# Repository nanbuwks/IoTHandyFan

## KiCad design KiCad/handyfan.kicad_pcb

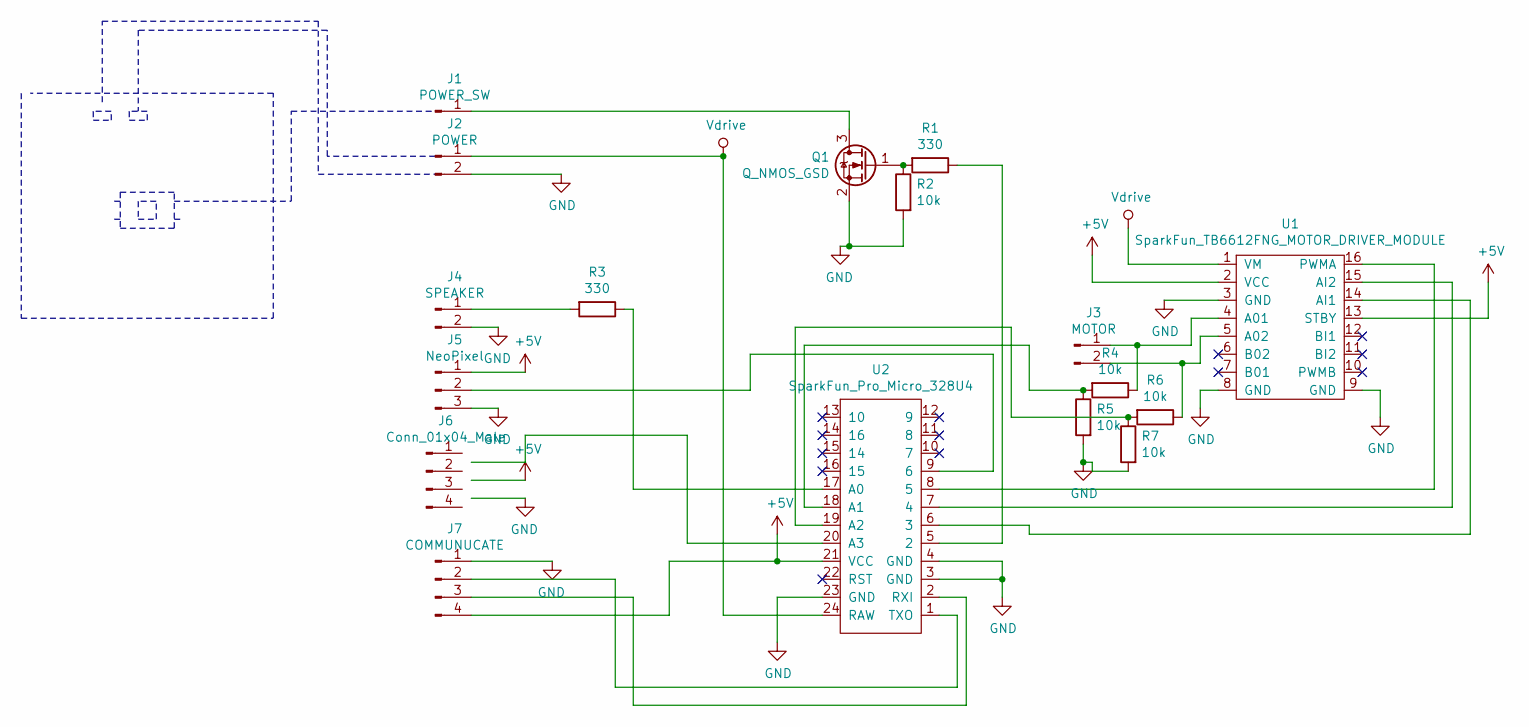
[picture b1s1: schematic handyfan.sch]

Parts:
J1: POWER_SW; PinHeader_1x01_P2.54mm_Vertical
J2: POWER; PinHeader_1x02_P2.54mm_Vertical
J3: MOTOR; PinHeader_1x02_P2.54mm_Vertical
J4: SPEAKER; PinHeader_1x02_P2.54mm_Vertical
J5: NeoPixel; PinHeader_1x03_P2.54mm_Vertical
J6: Conn_01x04_Male; JST_PH_B4B-PH-K_1x04_P2.00mm_Vertical
J7: COMMUNUCATE; PinHeader_1x04_P2.54mm_Vertical
Q1: Q_NMOS_GSD; SOT-23
R1, R3: 330; R_Axial_DIN0204_L3.6mm_D1.6mm_P7.62mm_Horizontal
R2, R4, R5, R6, R7: 10k; R_Axial_DIN0204_L3.6mm_D1.6mm_P7.62mm_Horizontal
U1: SparkFun_TB6612FNG_MOTOR_DRIVER_MODULE
U2: SparkFun_Pro_Micro_328U4; SparkFun_Pro_Micro_32U4

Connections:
+5V: J5.1, J7.4, U1.2 (VCC), U1.13 (STBY), U2.21 (VCC)
GND: J2.2, J4.2, J5.3, J7.1, Q1.2 (S), R2.2, R5.2, R7.2, U1.3 (GND), U1.8 (GND), U1.9 (GND), U2.3 (GND), U2.4 (GND), U2.23 (GND)
unnamed: J1.1, Q1.3 (D)
unnamed: J3.1, R4.1, U1.4 (A01)
unnamed: J3.2, R6.1, U1.5 (A02)
unnamed: J4.1, R3.2
unnamed: J5.2, U2.9 (6)
unnamed: J7.2, U2.1 (TXO)
unnamed: J7.3, U2.2 (RXI)
unnamed: Q1.1 (G), R1.2, R2.1
unnamed: R1.1, U2.5 (2)
unnamed: R3.1, U2.17 (A0)
unnamed: R4.2, R5.1, U2.18 (A1)
unnamed: R6.2, R7.1, U2.19 (A2)
unnamed: U1.14 (AI1), U2.6 (3)
unnamed: U1.15 (AI2), U2.7 (4)
unnamed: U1.16 (PWMA), U2.8 (5)
Vdrive: J2.1, U1.1 (VM), U2.24 (RAW)

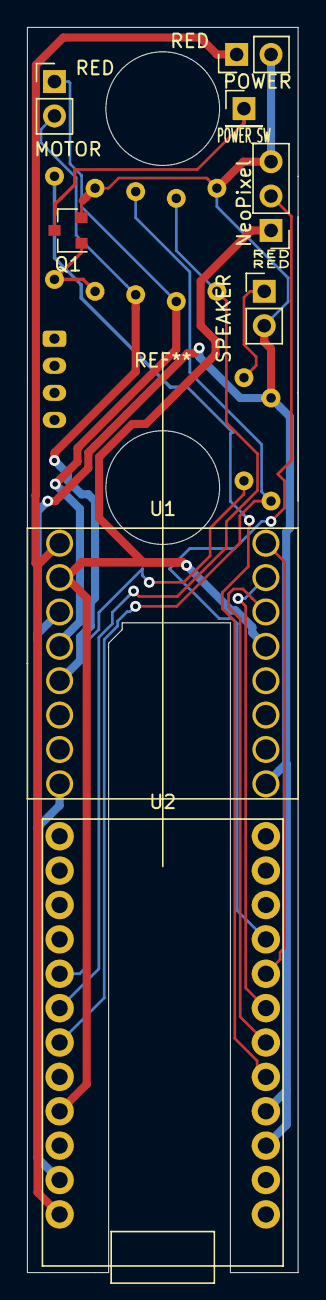
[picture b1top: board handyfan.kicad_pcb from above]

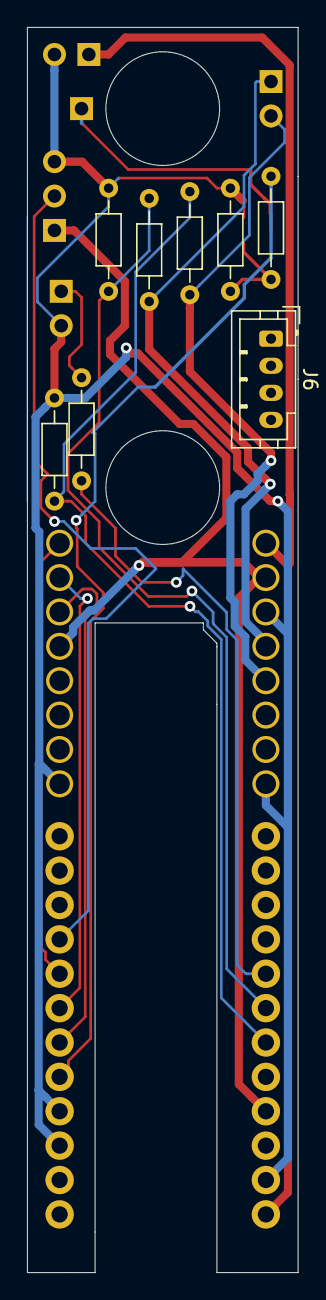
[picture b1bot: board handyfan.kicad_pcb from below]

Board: 2 copper layers, 20.0 x 92.0 mm, 16 parts (8 on the bottom side), 16 nets.

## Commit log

2019-08-27 KiCad files add.
